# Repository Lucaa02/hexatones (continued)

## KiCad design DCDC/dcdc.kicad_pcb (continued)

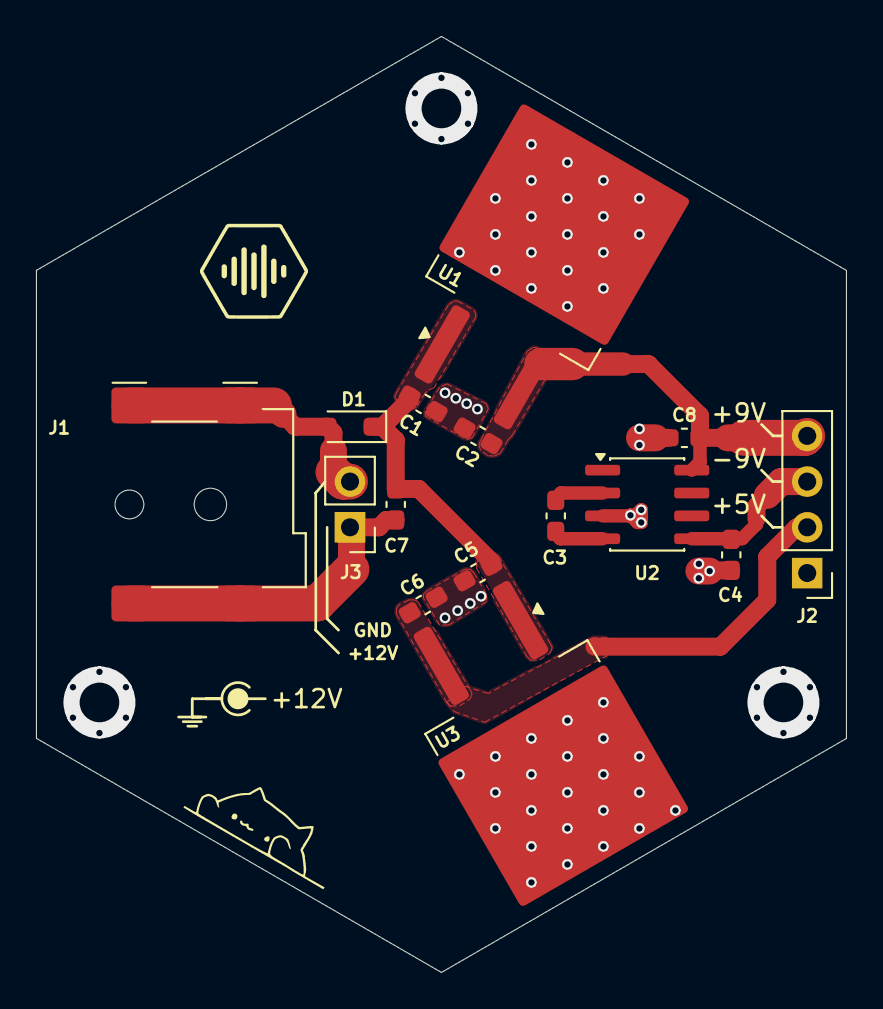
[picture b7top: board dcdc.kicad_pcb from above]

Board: 2 copper layers, 45.0 x 52.0 mm, 15 parts (0 on the bottom side), 8 nets.

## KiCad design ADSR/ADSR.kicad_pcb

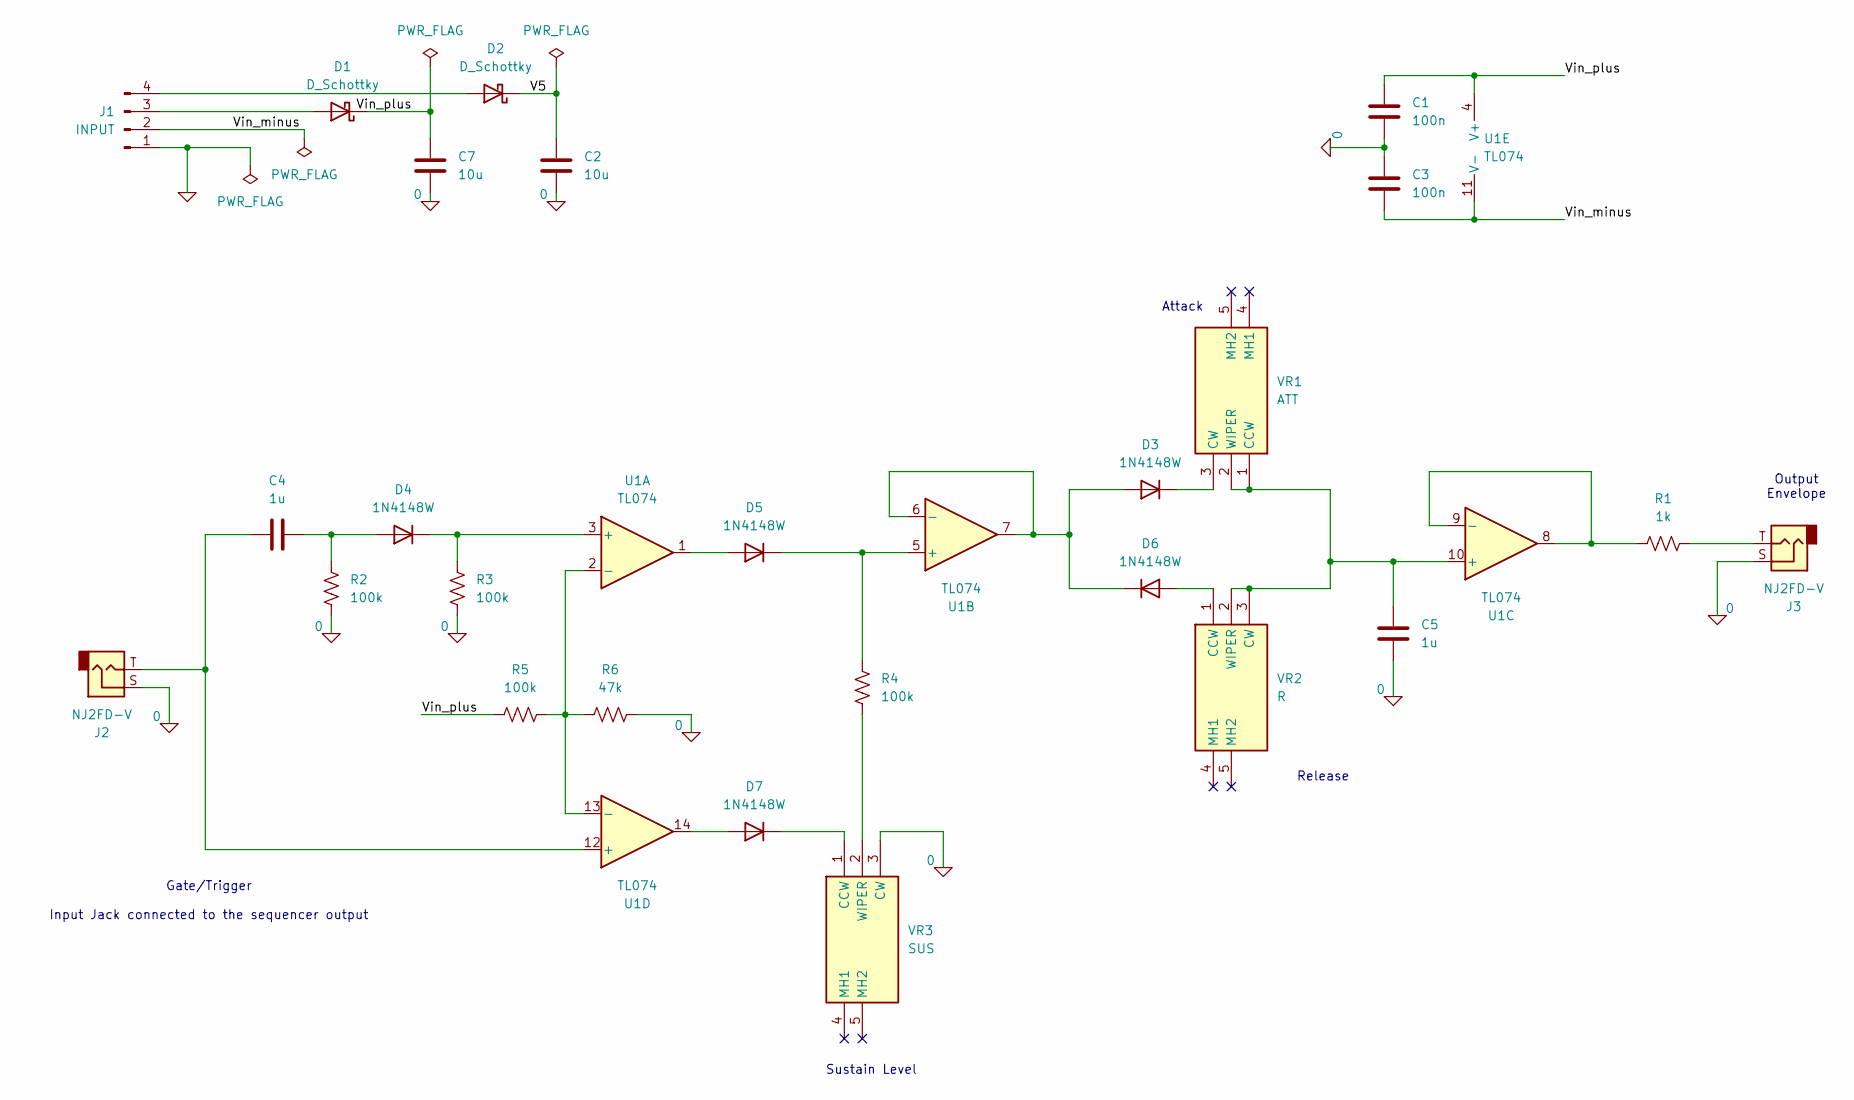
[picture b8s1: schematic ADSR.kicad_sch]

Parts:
C1, C3: 100n; C_0603_1608Metric_Pad1.08x0.95mm_HandSolder
C2, C7: 10u; C_0603_1608Metric_Pad1.08x0.95mm_HandSolder
C4, C5: 1u; C_0603_1608Metric_Pad1.08x0.95mm_HandSolder
D1, D2: D_Schottky; D_SOD-323_HandSoldering
D3, D4, D5, D6, D7: 1N4148W; D_SOD-123
J1: INPUT; PinHeader_1x04_P2.54mm_Vertical
J2, J3: NJ2FD-V; Jack_3.5mm_QingPu_WQP-PJ398SM_Vertical_CircularHoles
R1: 1k; R_0603_1608Metric_Pad0.98x0.95mm_HandSolder
R2, R3, R4, R5: 100k; R_0603_1608Metric_Pad0.98x0.95mm_HandSolder
R6: 47k; R_0603_1608Metric_Pad0.98x0.95mm_HandSolder
U1: TL074; SOIC-14_3.9x8.7mm_P1.27mm
VR1: ATT; Potentiometer_Alpha_RD901F-40-00D_Single_Vertical; Mouser Part Number 311-1940F-15R1-B100K
VR2: R; Potentiometer_Alpha_RD901F-40-00D_Single_Vertical; Mouser Part Number 311-1940F-15R1-B100K
VR3: SUS; Potentiometer_Alpha_RD901F-40-00D_Single_Vertical; Mouser Part Number 311-1940F-15R1-B100K

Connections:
0: C1.2, C2.2, C3.1, C5.2, C7.2, J1.1, J2.S, J3.S, R2.1, R3.1, R6.2, VR3.3 (CW)
/Vin_minus: C3.2, J1.2, U1.11 (V-)
/Vin_plus: C1.1, C7.1, D1.1 (K), R5.1, U1.4 (V+)
unnamed: C2.1, D2.1 (K)
unnamed: D1.2 (A), J1.3
unnamed: D2.2 (A), J1.4
unnamed: D3.2 (A), D6.1 (K), U1.6 (-), U1.7
unnamed: D3.1 (K), VR1.3 (CW)
unnamed: C4.2, D4.2 (A), R2.2
unnamed: D4.1 (K), R3.2, U1.3 (+)
unnamed: D5.2 (A), U1.1
unnamed: D5.1 (K), R4.2, U1.5 (+)
unnamed: D6.2 (A), VR2.1 (CCW)
unnamed: D7.2 (A), U1.14
unnamed: D7.1 (K), VR3.1 (CCW)
unnamed: J3.T, R1.1
unnamed: R5.2, R6.1, U1.2 (-), U1.13 (-)
unnamed: C5.1, U1.10 (+), VR1.1 (CCW), VR1.2 (WIPER), VR2.2 (WIPER), VR2.3 (CW)
unnamed: R1.2, U1.8, U1.9 (-)
unnamed: C4.1, J2.T, U1.12 (+)
unnamed: R4.1, VR3.2 (WIPER)

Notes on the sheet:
Release
Attack
Sustain Level
Gate/Trigger Input Jack connected to the sequencer output
Output Envelope

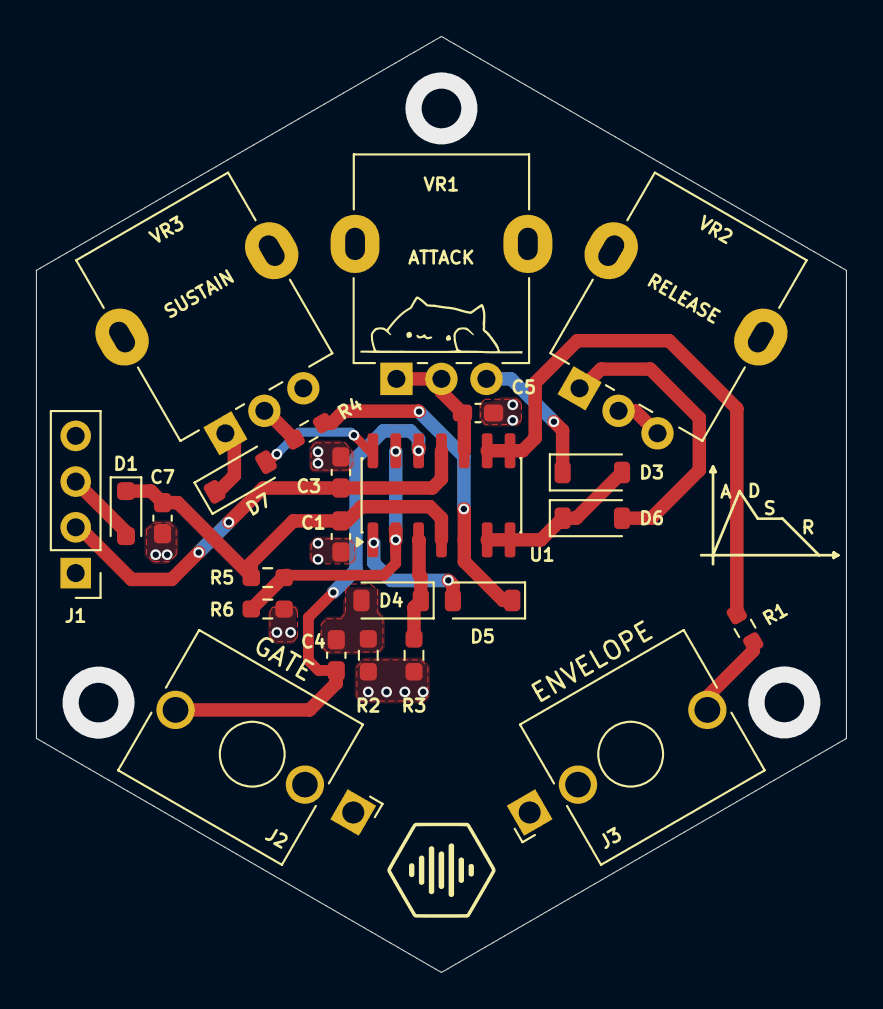
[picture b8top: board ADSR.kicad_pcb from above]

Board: 2 copper layers, 45.0 x 52.0 mm, 24 parts (0 on the bottom side), 19 nets.
